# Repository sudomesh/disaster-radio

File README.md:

[disaster.radio](https://disaster.radio) is currently not actively developed and [seeks a new maintainer](https://github.com/sudomesh/disaster-radio/issues/110)

It is a work-in-progress long-range, low-bandwidth wireless disaster recovery mesh network powered by the sun. 

* [firmware/](./firmware) contains the main example code for ESP32 dev boards
* [src/](./src) contains the disaster radio library code used by the firmware and simulator
* [web/](./web) is the demo chat app served up by the disaster-radio
* [hardware/](./hardware) is the kicad board layout and schematic
* [enclosure/](./enclosure) are 3D models of the enclosure(s)
* [android app](https://github.com/beegee-tokyo/disaster-radio-android) source code for [DisasterRadio BLE Chatbox](https://play.google.com/store/apps/details?id=tk.giesecke.disaster_radio&hl=en_US) Android Application
* [mapping web app](https://github.com/sudomesh/disaster-radio-map) source code for mapping web-based appilcation

## Table of contents
- [Getting Started](#getting-started)
- [Layout and Flow](#layout-and-flow)
- [Hardware Connections](#hardware-connections)
- [Initial Setup with PlatformIO](#initial-setup-with-platformio)
    - [Building firmware](#building-firmware)
    - [Flashing firmware](#flashing-firmware)
        - [For dev boards](#for-dev-boards)
- [Building Web App](#building-web-app)
    - [Building and uploading SPIFFS image](#building-and-uploading-SPIFFS-image)
- [Testing Firmware](#testing-firmware) 
- [Adding Libraries](#adding-libraries)
- [Creating Binary for Release](#creating-binary-for-release)
- [License](#license)

# Getting Started
The quickest way to get started with disaster.radio is to buy a <a href="https://www.aliexpress.com/item/4000396836096.html" target="_blank">preinstalled device</a> or
* Download the [latest release](https://github.com/sudomesh/disaster-radio/releases)
* Unzip the `disaster-radio-0.X.X.zip` file
* Follow the included instructions for flashing it to your device

If you would rather test the latest, cutting-edge developments, you can compile the firmware yourself by cloning this repo and following the [initial setup](#initial-setup-with-platformio) instructions.

# Layout and Flow
The Disaster Radio firmware is made up of a single "server" and a number of "clients", as well as "middleware" that sits between the clients and server. These are a"server" and "clients" in the logical, software sense, not a literal, networking sense.
 
Here are the modules currently implemented with descriptions of their purpose:
- DisasterServer:  
    - DisasterRadio: the main "server" that takes messages from clients and sends them to other clients

- DisasterClient:  
    - LoRaClient: interfaces with LoRaLayer2  
    - WebSocketClient: WebSocket connections from the web app  
    - StreamClient: for Arduino Stream, currently used for serial console  
    - TCPClient: for a telnet-like server  
    - HistoryRecord: records messages to SD card (or bounded queue in memory)  
    - OLEDClient: displays messages on the screen (mostly for debugging purposes, but eventually I'd like to use this for a mobile Disaster Radio terminal of some kind)   
    - GPSClient: proof-of-concept, interfaces with a serial GPS module to beacon your current location periodically  

- DisasterMiddleware:  
    - WelcomeMessage: (very simple, in main.cpp) shows a welcome message to clients when they connect
    - HistoryReplay: shows history to clients when they connect
    - Console: implements a simple console with chat (similar to the web app) plus some /commands (I went with a more IRC-like syntax but you could easily implement a getopt version)
    
- DisasterHistory:
    - HistorySD: records history to SD card
    - HistoryMemory: records history to a bounded queue in memory (default limit 10 messages)

The server and clients communicate with each other using "datagrams" that include a destination address, a message type, and a message. Read more about the disaster radio networking stack on our wiki, https://github.com/sudomesh/disaster-radio/wiki/Layered-Model.

# Hardware Connections  

For supported development boards see the [Devices & Hardware](https://github.com/sudomesh/disaster-radio/wiki/Devices--&-Hardware) wiki page.  

The pinouts for supported boards can be found in [firmware/esp32/config.h](https://github.com/sudomesh/disaster-radio/blob/master/firmware/esp32/config.h).  

DIO0 sends an interrupt from the LoRa transceiver upon Tx/Rx Ready on the radio.   
Chip selects can be used to explicitly switch between the LoRa tranceiver and the SD card; however, the SD card should be enabled by default, as the LoRa interrupt appears to handle enabling the transceiver (note: this still needs to be thoroughly tested, what happens if you receive an interrupt while loading from the SD?).  

# Initial Setup with PlatformIO

```
pip install -U platformio
```

Edit `platformio.ini` to suit your needs. If you are flashing a ESP32 LILY TTGO board then you will probably not have to edit anything in `platformio.ini` but make sure `upload_port` is set to the correct device which may vary depending on your operating system and which other devices you have connected.

## Building firmware

To test that the firmware is compiling correctly without flashing it to a device, run
```
pio run
```

This will compile all libraries and main firmware files. The resulting binary is stored as `.pio/build/ttgo-lora32-v1/firmware.bin`

## Flashing firmware

### For dev boards

Connect your computer to the board using a usb cable,

In `platformio.ini` make sure `upload_port`, `upload_speed`, etc are correct for your device.

Then run:

```
pio run -t upload
```
 
By default, PlatformIO builds and flashes firmware for the LILY's ESP32 TTGO V2 dev board. If you would like to build for another supported board, select the corresponding build environment. For example to build and flash the firmware and file system for the ESP32 TTG0 V1 board, use the following, 

```
pio run -e ttgo-lora32-v1 -t upload -t uploadfs

```

## Developing firmware

Some useful hints for developing this firmware using platformio are included here,
* It may be a good idea to delete the libdeps folder prior to rebuilding, as old, out-dated libraries could case conflits. To do this, `rm -rf .pio/libdeps`.
* If you would like to make changes to a specific library, such as LoRaLayer2, you can clone the library into the `firmware/lib` folder that is created after running `pio run` and then comment it out or remove it from the `lib_deps` list in the `platformio.ini` file.

# Building Web App

First, build the web app using npm, instructions for can be found in [web/README.md](https://github.com/sudomesh/disaster-radio/tree/master/web#setup).

If you have trouble building the web app with npm, you can download a pre-built version of web app as part of the [latest release](https://github.com/sudomesh/disaster-radio/releases). Then, copy the files in `web/static/` from the zipped release to the `web/static/` directory in the cloned repo.

## Building and uploading SPIFFS image

Next, build the binary for the SPIFFS and upload it to your board.

To only build:

```
pio run -t buildfs
```

To build and upload:

```
pio run -t uploadfs
```

If using an SD card, copy the contents of `web/static/` to the root of a fat32 formatted SD card, then insert the SD card.

# Testing Firmware  
Once the firmware and SPIFFS image has been successfully flashed, you can test it by logging into the `disaster.radio <node-address>` wireless network and navigating to http://192.168.4.1 in a browser to access the demo chat app.  

You can also try connecting to the device via serial or telnet with commands like,  
```
pio device monitor
```
or
```
telnet 192.168.4.1
```

After pressing enter once, you should be greeted with a banner and presented with a prompt to enter a nick or send an anonymous message,
```
     ___              __                            ___    
 ___/ (_)__ ___ ____ / /____ ____      _______ ____/ (_)__ 
/ _  / (_-</ _ `(_-</ __/ -_) __/ _   / __/ _ `/ _  / / _ \
\_,_/_/___/\_,_/___/\__/\__/_/   (_) /_/  \_,_/\_,_/_/\___/
v1.0.0-rc.2
LoRa transceiver connected
Local address of your node is 1d69bd4c
Type '/join NICKNAME' to join the chat, or '/help' for more commands.
< > 
```

See [firmware/README.md](https://github.com/sudomesh/disaster-radio/tree/master/firmware) for more debugging information.

# Adding Libraries

If you're including new libraries in the firmware, for PlatformIO, you wil need to add them to `platformio.ini` under `lib_deps`.

# Creating Binary for Release

A full binary image can be created by reading the flash contents of a ESP32 that is flashed with the latest release of the firmware.
To do this, run the following command,
```
esptool.py -p /dev/ttyUSB0 -b 921600 read_flash 0 0x400000 esp_flash.bin
```

This can then be flashed to a new device like so,
```
esptool.py -p /dev/ttyUSB0 --baud 460800 write_flash 0x00000 esp_flash.bin
```

# License

* `firmware/`: Dual licensed under both GPLv3 and AGPLv3
* `web/`: AGPLv3

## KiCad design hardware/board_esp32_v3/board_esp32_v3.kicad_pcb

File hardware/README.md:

# Hardware

The disaster.radio hardware is as open-as-possible. Currently, we have the schematic, BOM, and circuit board design for a development board that you can, theoretically, print yourself or order from a circuit board manufacturer of your choice. 

## Features
* ESP32-WROOM integrated WiFi + BLE microcontroller
* Dual LoRa modules
* Micro-SD card slot
* Micro-USB port for serial debugging
* Battery connection
* Battery charging module (currently using TPS6216)

## Developement
Our hardware was designed in KiCad, if you would like to edit the board deisgn or take a closer look at the schematics you can [download and install KiCad](https://kicad-pcb.org/download/) for your system.

After installing, open KiCad, choose `File > Open Project...`, navigate to where you cloned this repo, and select the file `hardware/board_esp32_v2/board_esp32_v2.pro`. You can now open and view the schematic and pcb design.

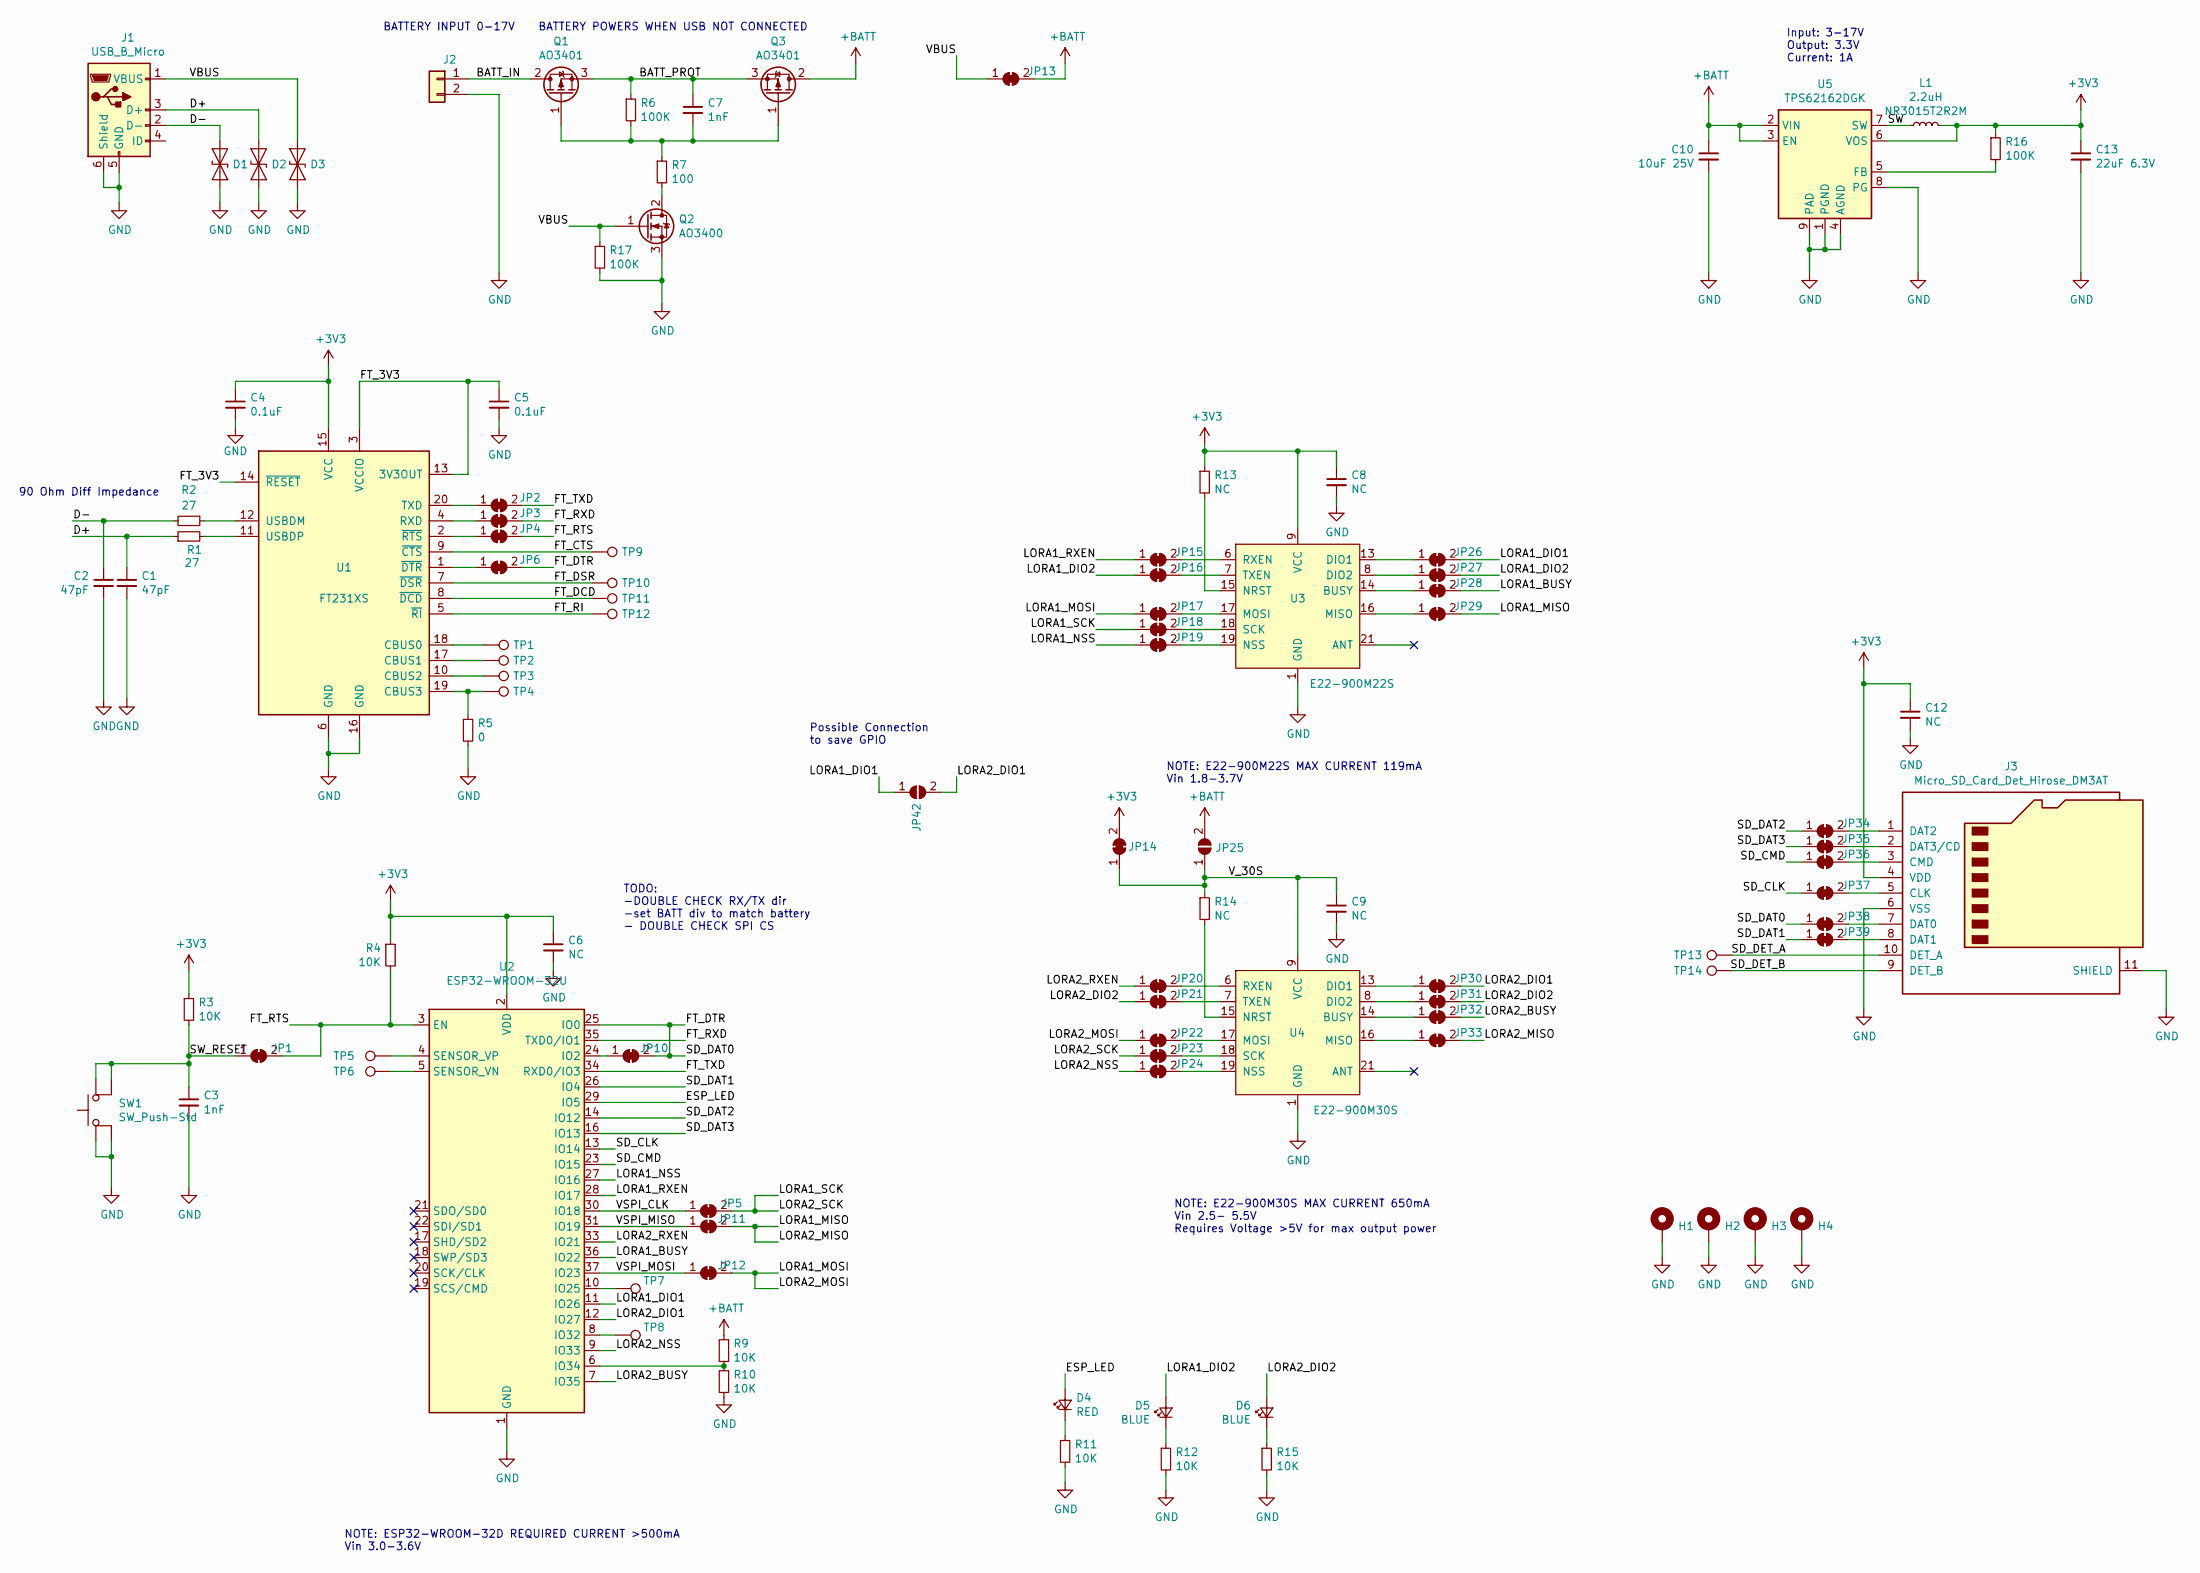
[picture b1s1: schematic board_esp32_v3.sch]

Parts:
C1, C2: 47pF; C_0402_1005Metric
C3, C7: 1nF; C_0402_1005Metric
C4, C5: 0.1uF; C_0402_1005Metric
C6, C8, C9, C12: NC; C_0402_1005Metric
C10: 10uF 25V; C_0805_2012Metric
C13: 22uF 6.3V; C_0805_2012Metric
D1, D2, D3: TPD1E10B06; D_0402_1005Metric
D4: RED; LED_0603_1608Metric
D5, D6: BLUE; LED_0603_1608Metric
H1, H2, H3, H4: MountingHole_Pad; MountingHole_2.2mm_M2_ISO7380_Pad
J1: USB_B_Micro; USB_Micro-B_GCT_USB3076-30-A_handsolder
J2: Conn_01x02; PinHeader_1x02_P2.54mm_Vertical
J3: Micro_SD_Card_Det_Hirose_DM3AT; microSD_HC_Hirose_DM3D-SF
JP1, JP2, JP3, JP4, JP5, JP6, JP10, JP11, JP12, JP13, JP14, JP15, JP16, JP17, JP18, JP19, JP20, JP21, JP22, JP23, JP24, JP26, JP27, JP28, JP29, JP30, JP31, JP32, JP33, JP34, JP35, JP36, JP37, JP38, JP39: SolderJumper_2_Bridged; SolderJumper-2_P1.3mm_Bridged_RoundedPad1.0x1.5mm
JP25, JP42: SolderJumper_2_Open; SolderJumper-2_P1.3mm_Open_RoundedPad1.0x1.5mm
L1: 2.2uH; L_Taiyo-Yuden_NR-30xx_HandSoldering; MPN NR3015T2R2M
Q1, Q3: AO3401; SOT-23
Q2: AO3400; SOT-23
R1, R2: 27; R_0402_1005Metric
R3, R4, R9, R10, R11, R12, R15: 10K; R_0402_1005Metric
R5: 0; R_0402_1005Metric
R6, R16, R17: 100K; R_0402_1005Metric
R7: 100; R_0402_1005Metric
R13, R14: NC; R_0402_1005Metric
SW1: SW_Push-Std; SW_PUSH_6mm
TP1, TP2, TP3, TP4, TP9, TP10, TP11, TP12, TP13, TP14: TestPoint; TestPoint_Pad_D1.0mm
TP5, TP6, TP7, TP8: TP_HOLE; TestPoint_Pad_D1.0mm
U1: FT231XS; SSOP-20_3.9x8.7mm_P0.635mm
U2: ESP32-WROOM-32U
U3: E22-900M22S; E22_900T22S
U4: E22-900M30S
U5: TPS62162DGK; TPS62162DSGT

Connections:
+3V3: C4.1, C6.1, C8.1, C12.1, C13.1, J3.4 (VDD), JP14.2 (B), L1.2, R3.1, R4.1, R13.1, R16.1, U1.15 (VCC), U2.2 (VDD), U3.9 (VCC), U5.6 (VOS)
+BATT: C10.1, JP13.2 (B), JP25.2 (B), Q3.2 (D), R9.1, U5.2 (VIN), U5.3 (EN)
/BATT_IN: J2.1, Q1.2 (D)
/BATT_PROT: C7.1, Q1.3 (S), Q3.3 (S), R6.1
/D+: C1.1, D2.1 (A1), J1.3 (D+), R1.1
/D-: C2.1, D1.1 (A1), J1.2 (D-), R2.2
/ESP_LED: D4.2 (A), U2.29 (IO5)
/FT_3V3: C5.1, U1.3 (VCCIO), U1.13 (3V3OUT), U1.14 (~RESET)
/FT_CTS: TP9.1, U1.9 (~CTS)
/FT_DCD: TP11.1, U1.8 (~DCD)
/FT_DSR: TP10.1, U1.7 (~DSR)
/FT_DTR: JP6.2 (B), JP10.2 (B), JP38.1 (A), U2.25 (IO0)
/FT_RI: TP12.1, U1.5 (~RI)
/FT_RTS: JP1.2 (B), JP4.2 (B), R4.2, U2.3 (EN)
/FT_RXD: JP3.2 (B), U2.35 (TXD0/IO1)
/FT_TXD: JP2.2 (B), U2.34 (RXD0/IO3)
/LORA1_BUSY: JP28.2 (B), U2.36 (IO22)
/LORA1_DIO1: JP26.2 (B), JP42.1 (A), U2.11 (IO26)
/LORA1_DIO2: D5.2 (A), JP16.1 (A), JP27.2 (B)
/LORA1_MISO: JP11.2 (B), JP29.2 (B), JP33.2 (B)
/LORA1_MOSI: JP12.2 (B), JP17.1 (A), JP22.1 (A)
/LORA1_NSS: JP19.1 (A), U2.27 (IO16)
/LORA1_RXEN: JP15.1 (A), U2.28 (IO17)
/LORA1_SCK: JP5.2 (B), JP18.1 (A), JP23.1 (A)
/LORA2_BUSY: JP32.2 (B), U2.7 (IO35)
/LORA2_DIO1: JP30.2 (B), JP42.2 (B), U2.12 (IO27)
/LORA2_DIO2: D6.2 (A), JP21.1 (A), JP31.2 (B)
/LORA2_NSS: JP24.1 (A), U2.9 (IO33)
/LORA2_RXEN: JP20.1 (A), U2.33 (IO21)
/SD_CLK: JP37.1 (A), U2.13 (IO14)
/SD_CMD: JP36.1 (A), U2.23 (IO15)
/SD_DAT1: JP39.1 (A), U2.26 (IO4)
/SD_DAT2: JP34.1 (A), U2.14 (IO12)
/SD_DAT3: JP35.1 (A), U2.16 (IO13)
/SD_DET_A: J3.10 (DET_A), TP13.1
/SD_DET_B: J3.9 (DET_B), TP14.1
/SW: L1.1, U5.7 (SW)
/SW_RESET: C3.1, JP1.1 (A), R3.2, SW1.2
/VBUS: D3.1 (A1), J1.1 (VBUS), JP13.1 (A), Q2.1 (G), R17.1
/VSPI_CLK: JP5.1 (A), U2.30 (IO18)
/VSPI_MISO: JP11.1 (A), U2.31 (IO19)
/VSPI_MOSI: JP12.1 (A), U2.37 (IO23)
/V_30S: C9.1, JP14.1 (A), JP25.1 (A), R14.1, U4.9 (VCC), U4.10 (VCC)
GND: C1.2, C2.2, C3.2, C4.2, C5.2, C6.2, C8.2, C9.2, C10.2, C12.2, C13.2, D1.2 (A2), D2.2 (A2), D3.2 (A2), H1.1, H2.1, H3.1, H4.1, J1.5 (GND), J1.6 (Shield), J2.2, J3.6 (VSS), J3.11 (SHIELD), Q2.3 (S), R5.2, R10.2, R11.2, R12.2, R15.2, R17.2, SW1.1, U1.6 (GND), U1.16 (GND), U2.1 (GND), U2.15 (GND), U2.38 (GND), U2.39 (GND), U3.1 (GND), U3.2 (GND), U3.3 (GND), U3.4 (GND), U3.5 (GND), U3.10 (GND), U3.11 (GND), U3.12 (GND), U3.20 (GND), U3.22 (GND), U4.1 (GND), U4.2 (GND), U4.3 (GND), U4.4 (GND), U4.5 (GND), U4.11 (GND), U4.12 (GND), U4.20 (GND), U4.22 (GND), U5.1 (PGND), U5.4 (AGND), U5.8 (PG), U5.9 (PAD)
unnamed: C7.2, Q1.1 (G), Q3.1 (G), R6.2, R7.1
unnamed: D4.1 (K), R11.1
unnamed: D5.1 (K), R12.1
unnamed: D6.1 (K), R15.1
unnamed: J3.1 (DAT2), JP34.2 (B)
unnamed: J3.2 (DAT3/CD), JP35.2 (B)
unnamed: J3.3 (CMD), JP36.2 (B)
unnamed: J3.5 (CLK), JP37.2 (B)
unnamed: J3.7 (DAT0), JP38.2 (B)
unnamed: J3.8 (DAT1), JP39.2 (B)
unnamed: JP2.1 (A), U1.20 (TXD)
unnamed: JP3.1 (A), U1.4 (RXD)
unnamed: JP4.1 (A), U1.2 (~RTS)
unnamed: JP6.1 (A), U1.1 (~DTR)
unnamed: JP10.1 (A), U2.24 (IO2)
unnamed: JP15.2 (B), U3.6 (RXEN)
unnamed: JP16.2 (B), U3.7 (TXEN)
unnamed: JP17.2 (B), U3.17 (MOSI)
unnamed: JP18.2 (B), U3.18 (SCK)
unnamed: JP19.2 (B), U3.19 (NSS)
unnamed: JP20.2 (B), U4.6 (RXEN)
unnamed: JP21.2 (B), U4.7 (TXEN)
unnamed: JP22.2 (B), U4.17 (MOSI)
unnamed: JP23.2 (B), U4.18 (SCK)
unnamed: JP24.2 (B), U4.19 (NSS)
unnamed: JP26.1 (A), U3.13 (DIO1)
unnamed: JP27.1 (A), U3.8 (DIO2)
unnamed: JP28.1 (A), U3.14 (BUSY)
unnamed: JP29.1 (A), U3.16 (MISO)
unnamed: JP30.1 (A), U4.13 (DIO1)
unnamed: JP31.1 (A), U4.8 (DIO2)
unnamed: JP32.1 (A), U4.14 (BUSY)
unnamed: JP33.1 (A), U4.16 (MISO)
unnamed: Q2.2 (D), R7.2
unnamed: R1.2, U1.11 (USBDP)
unnamed: R2.1, U1.12 (USBDM)
unnamed: R5.1, TP4.1, U1.19 (CBUS3)
unnamed: R9.2, R10.1, U2.6 (IO34)
unnamed: R13.2, U3.15 (NRST)
unnamed: R14.2, U4.15 (NRST)
unnamed: R16.2, U5.5 (FB)
unnamed: TP1.1, U1.18 (CBUS0)
unnamed: TP2.1, U1.17 (CBUS1)
unnamed: TP3.1, U1.10 (CBUS2)
unnamed: TP5.1, U2.4 (SENSOR_VP)
unnamed: TP6.1, U2.5 (SENSOR_VN)
unnamed: TP7.1, U2.10 (IO25)
unnamed: TP8.1, U2.8 (IO32)

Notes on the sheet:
90 Ohm Diff Impedance
NOTE: ESP32-WROOM-32D REQUIRED CURRENT >500mA Vin 3.0-3.6V
BATTERY INPUT 0-17V
BATTERY POWERS WHEN USB NOT CONNECTED
TODO: -DOUBLE CHECK RX/TX dir -set BATT div to match battery - DOUBLE CHECK SPI CS
Possible Connection to save GPIO
NOTE: E22-900M22S MAX CURRENT 119mA Vin 1.8-3.7V
NOTE: E22-900M30S MAX CURRENT 650mA Vin 2.5- 5.5V Requires Voltage >5V for max output power
Input: 3-17V Output: 3.3V Current: 1A

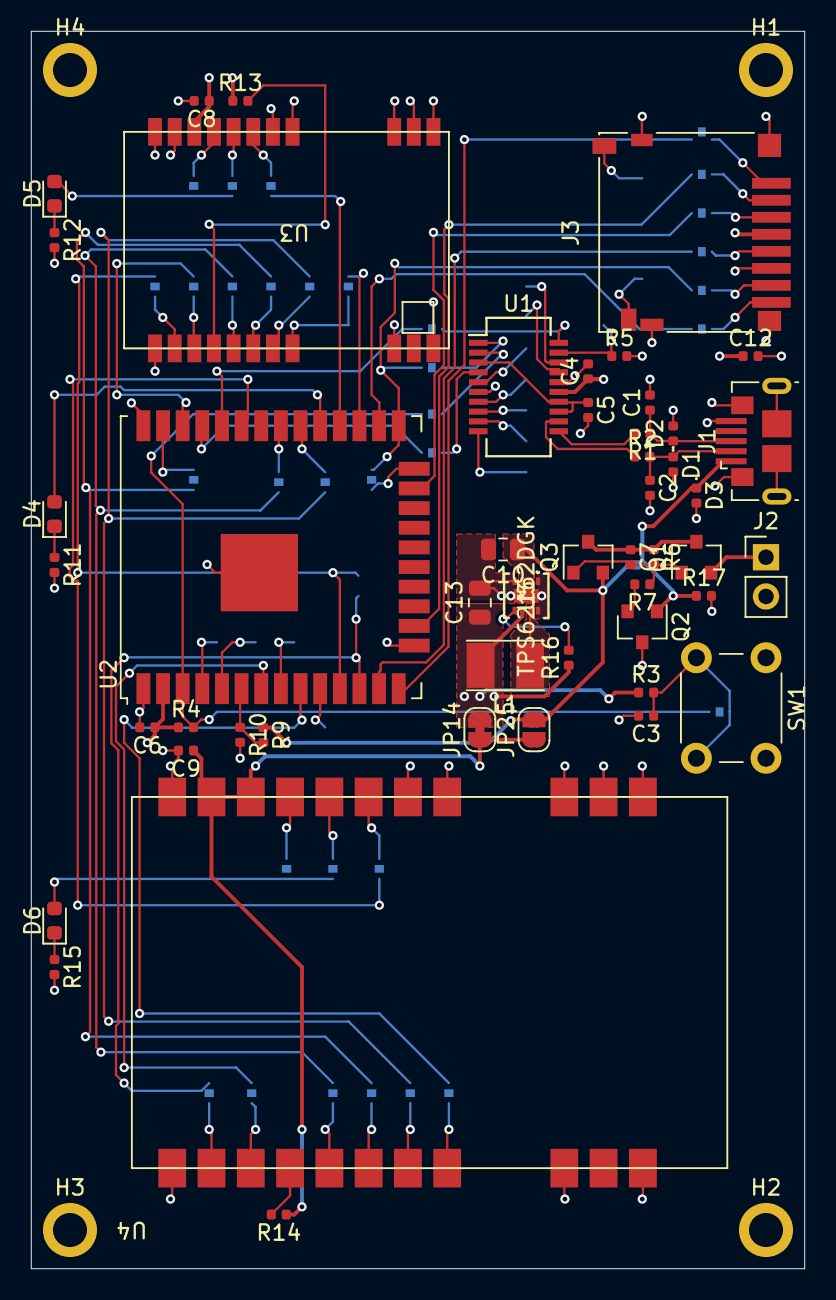
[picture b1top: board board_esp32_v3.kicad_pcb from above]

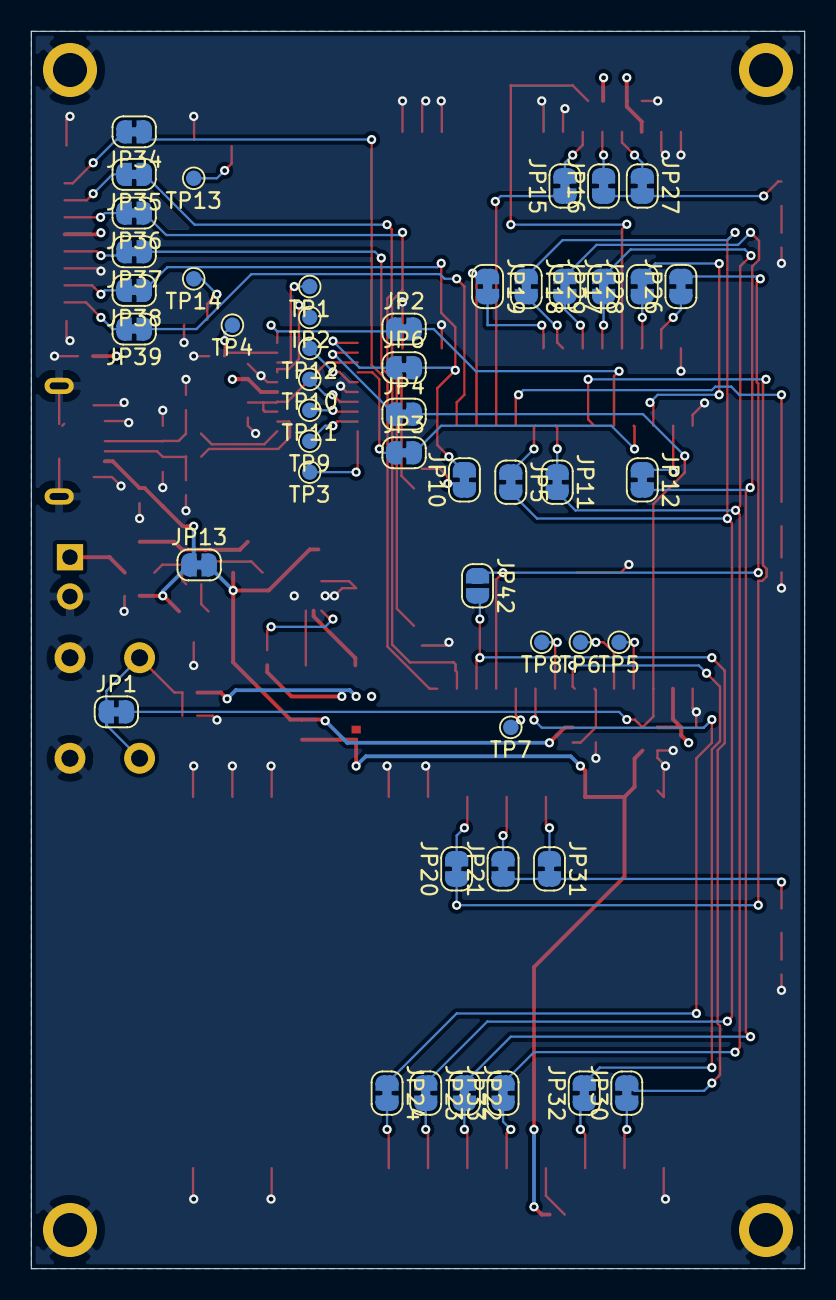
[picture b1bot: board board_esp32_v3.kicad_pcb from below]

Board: 4 copper layers, 50.0 x 80.0 mm, 102 parts (49 on the bottom side), 92 nets.

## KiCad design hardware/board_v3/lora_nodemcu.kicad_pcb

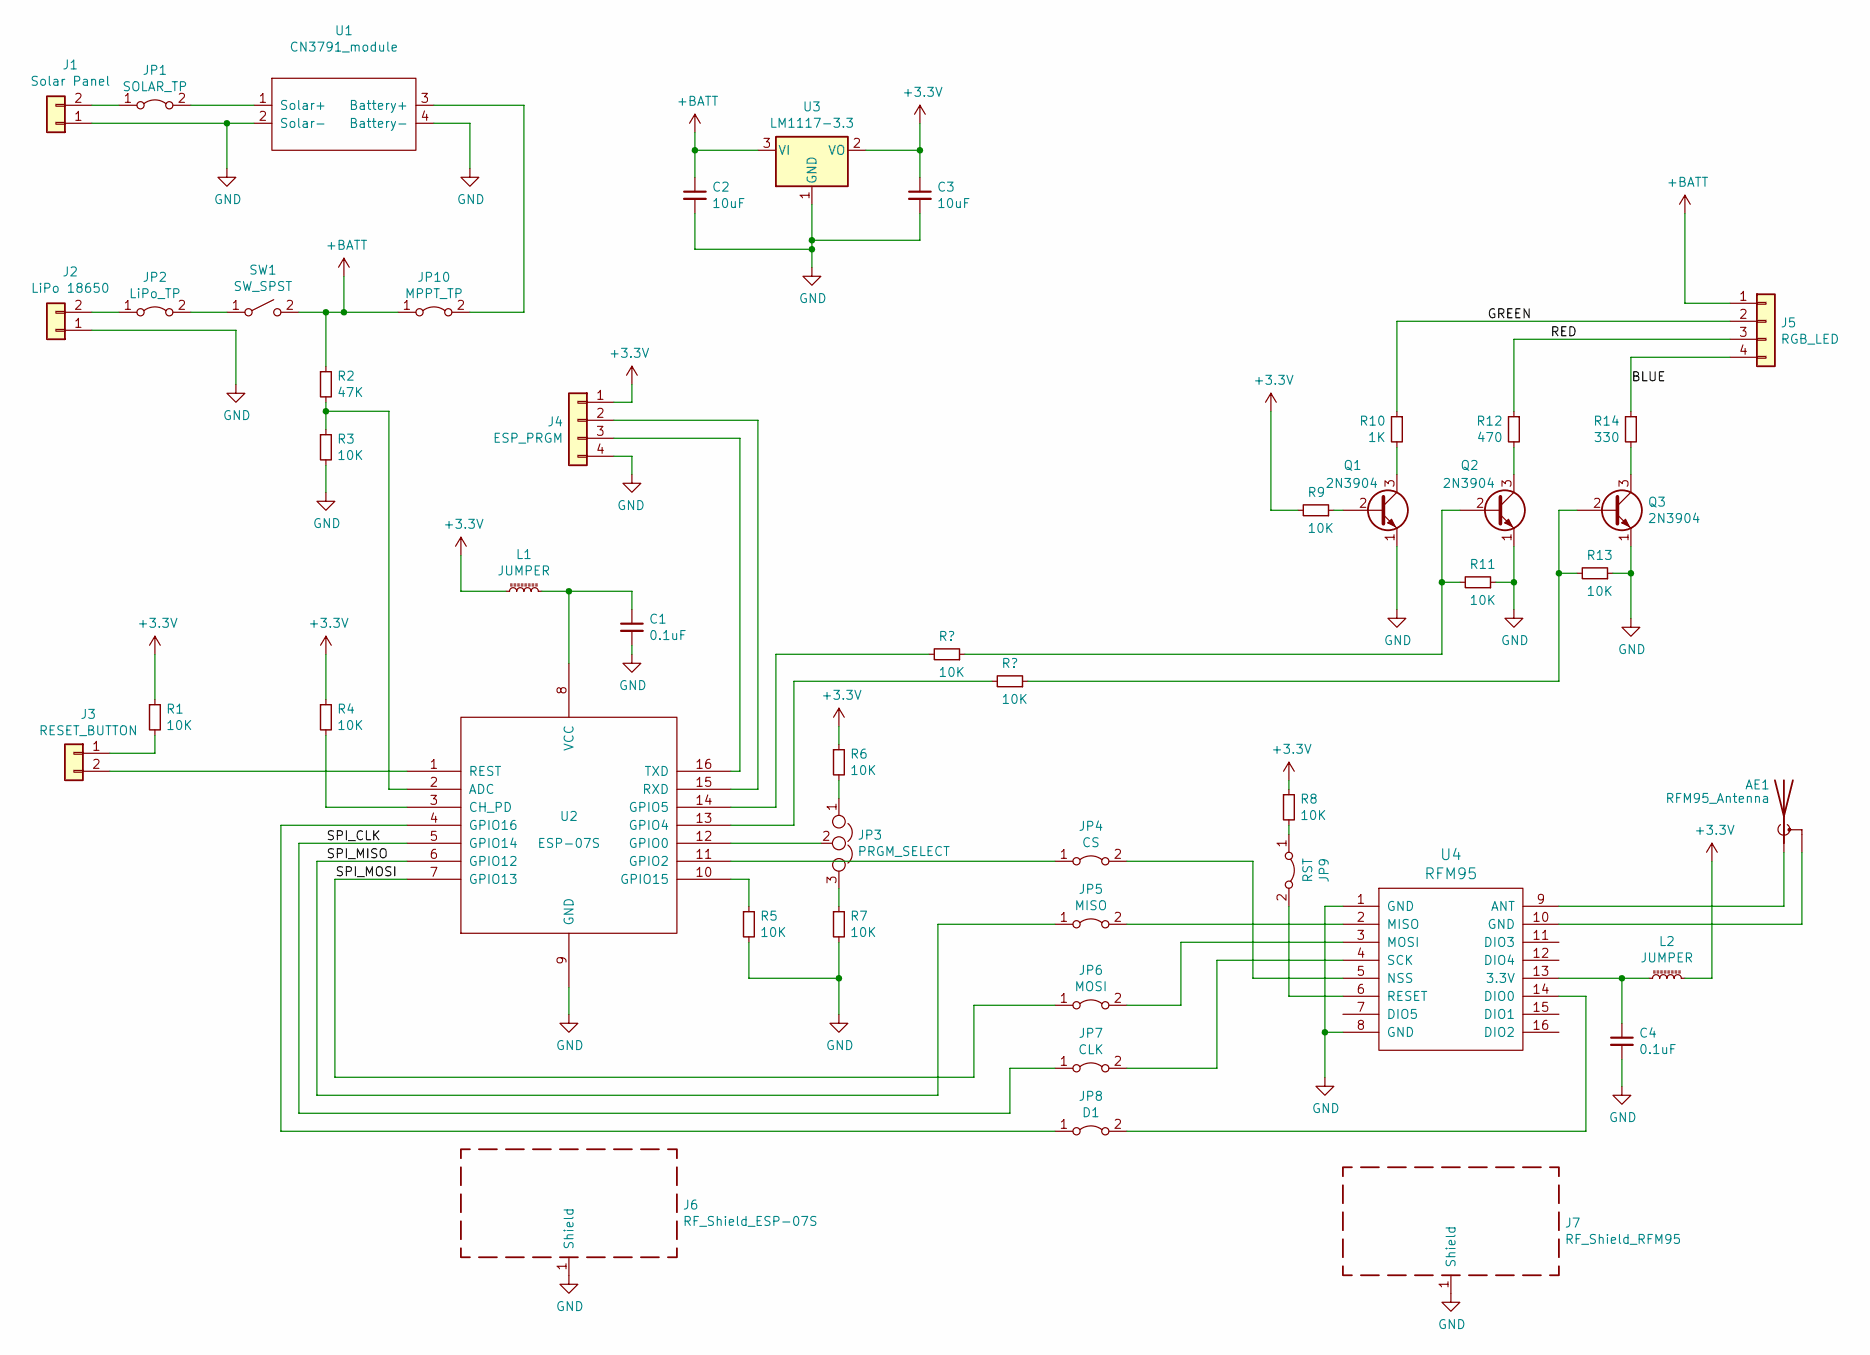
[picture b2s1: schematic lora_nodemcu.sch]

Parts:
AE1: RFM95_Antenna; U.FL_Hirose_U.FL-R-SMT-1_Vertical
C1, C4: 0.1uF; C_0805_2012Metric_Pad1.15x1.50mm_HandSolder
C2, C3: 10uF; C_0805_2012Metric_Pad1.15x1.50mm_HandSolder
J1: Solar Panel; PhoenixContact_MCV_1,5_2-G-5.08_1x02_P5.08mm_Vertical
J2: LiPo 18650; BatteryHolder_MPD_BH-18650-PC2
J3: RESET_BUTTON; PhoenixContact_MCV_1,5_2-G-5.08_1x02_P5.08mm_Vertical
J4: ESP_PRGM; PinHeader_1x04_P2.54mm_Vertical
J5: RGB_LED; PhoenixContact_MCV_1,5_4-G-5.08_1x04_P5.08mm_Vertical
J6: RF_Shield_ESP-07S; Wuerth_36103305_30x30mm
J7: RF_Shield_RFM95; Wuerth_36103305_30x30mm
JP1: SOLAR_TP; SolderJumper-2_P1.3mm_Bridged_Pad1.0x1.5mm
JP2: LiPo_TP; SolderJumper-2_P1.3mm_Bridged_Pad1.0x1.5mm
JP3: PRGM_SELECT; PinHeader_1x03_P2.54mm_Vertical
JP4: CS; SolderJumper-2_P1.3mm_Bridged_Pad1.0x1.5mm
JP5: MISO; SolderJumper-2_P1.3mm_Bridged_Pad1.0x1.5mm
JP6: MOSI; SolderJumper-2_P1.3mm_Bridged_Pad1.0x1.5mm
JP7: CLK; SolderJumper-2_P1.3mm_Bridged_Pad1.0x1.5mm
JP8: D1; SolderJumper-2_P1.3mm_Bridged_Pad1.0x1.5mm
JP9: RST; SolderJumper-2_P1.3mm_Bridged_Pad1.0x1.5mm
JP10: MPPT_TP; SolderJumper-2_P1.3mm_Bridged_Pad1.0x1.5mm
L1, L2: JUMPER; L_0805_2012Metric_Pad1.15x1.50mm_HandSolder
Q1, Q2, Q3: 2N3904; SOT-23_Handsoldering
R1, R3, R4, R5, R6, R7, R8, R9, R11, R13: 10K; R_0805_2012Metric_Pad1.15x1.50mm_HandSolder
R2: 47K; R_0805_2012Metric_Pad1.15x1.50mm_HandSolder
R10: 1K; R_0805_2012Metric_Pad1.15x1.50mm_HandSolder
R12: 470; R_0805_2012Metric_Pad1.15x1.50mm_HandSolder
R14: 330; R_0805_2012Metric_Pad1.15x1.50mm_HandSolder
SW1: SW_SPST; PhoenixContact_MCV_1,5_2-G-5.08_1x02_P5.08mm_Vertical
U1: CN3791_module
U2: ESP-07S
U3: LM1117-3.3; SOT-223-3_TabPin2
U4: RFM95

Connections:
+3V3: C3.1, J4.1, L1.1, L2.2, R1.1, R4.1, R6.1, R8.1, R9.2, U3.2 (VO)
+BATT: C2.1, J5.1, JP10.1 (A), R2.1, SW1.2 (B), U3.3 (VI); also elsewhere on the board
/3V3_ESP: C1.1, L1.2, U2.8 (VCC)
/3V3_RFM: C4.1, L2.1, U4.13 (3.3V)
/BATT_TP: JP10.2 (B), U1.3 (Battery+)
/BLUE: J5.4, R14.1; also elsewhere on the board
/GREEN: J5.2, R10.1; also elsewhere on the board
/LIPO_TP: JP2.2 (B), SW1.1 (A)
/RED: J5.3, R12.1; also elsewhere on the board
/SOLAR_CONN: J1.2, JP1.1 (A)
/SOLAR_TP: JP1.2 (B), U1.1 (Solar+)
/SPI_CLK: JP7.1 (A), U2.5 (GPIO14)
/SPI_MISO: JP5.1 (A), U2.6 (GPIO12)
/SPI_MOSI: JP6.1 (A), U2.7 (GPIO13)
unnamed: AE1.1 (A), U4.9 (ANT)
unnamed: AE1.2 (Shield), U4.10 (GND)
unnamed: J3.1, R1.2
unnamed: J3.2, U2.1 (REST)
unnamed: J4.2, U2.15 (RXD)
unnamed: J4.3, U2.16 (TXD)
unnamed: JP3.1, R6.2
unnamed: JP3.2, U2.12 (GPIO0)
unnamed: JP3.3, R7.1
unnamed: JP4.1 (A), U2.11 (GPIO2)
unnamed: JP4.2 (B), U4.5 (NSS)
unnamed: JP5.2 (B), U4.2 (MISO)
unnamed: JP6.2 (B), U4.3 (MOSI)
unnamed: JP7.2 (B), U4.4 (SCK)
unnamed: JP8.1 (A), U2.4 (GPIO16)
unnamed: JP8.2 (B), U4.14 (DIO0)
unnamed: JP9.1 (A), R8.2
unnamed: JP9.2 (B), U4.6 (RESET)
unnamed: Q1.2 (B), R9.1
unnamed: Q1.3 (C), R10.2
unnamed 34: Q2.2 (B), R11.2; also elsewhere on the board
unnamed: Q2.3 (C), R12.2
unnamed 36: Q3.2 (B), R13.2; also elsewhere on the board
unnamed: Q3.3 (C), R14.2
unnamed: R2.2, R3.1, U2.2 (ADC)
unnamed: R4.2, U2.3 (CH_PD)
unnamed: R5.1, U2.10 (GPIO15)
unnamed 41: U2.14 (GPIO5); also elsewhere on the board
unnamed 42: U2.13 (GPIO4); also elsewhere on the board

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
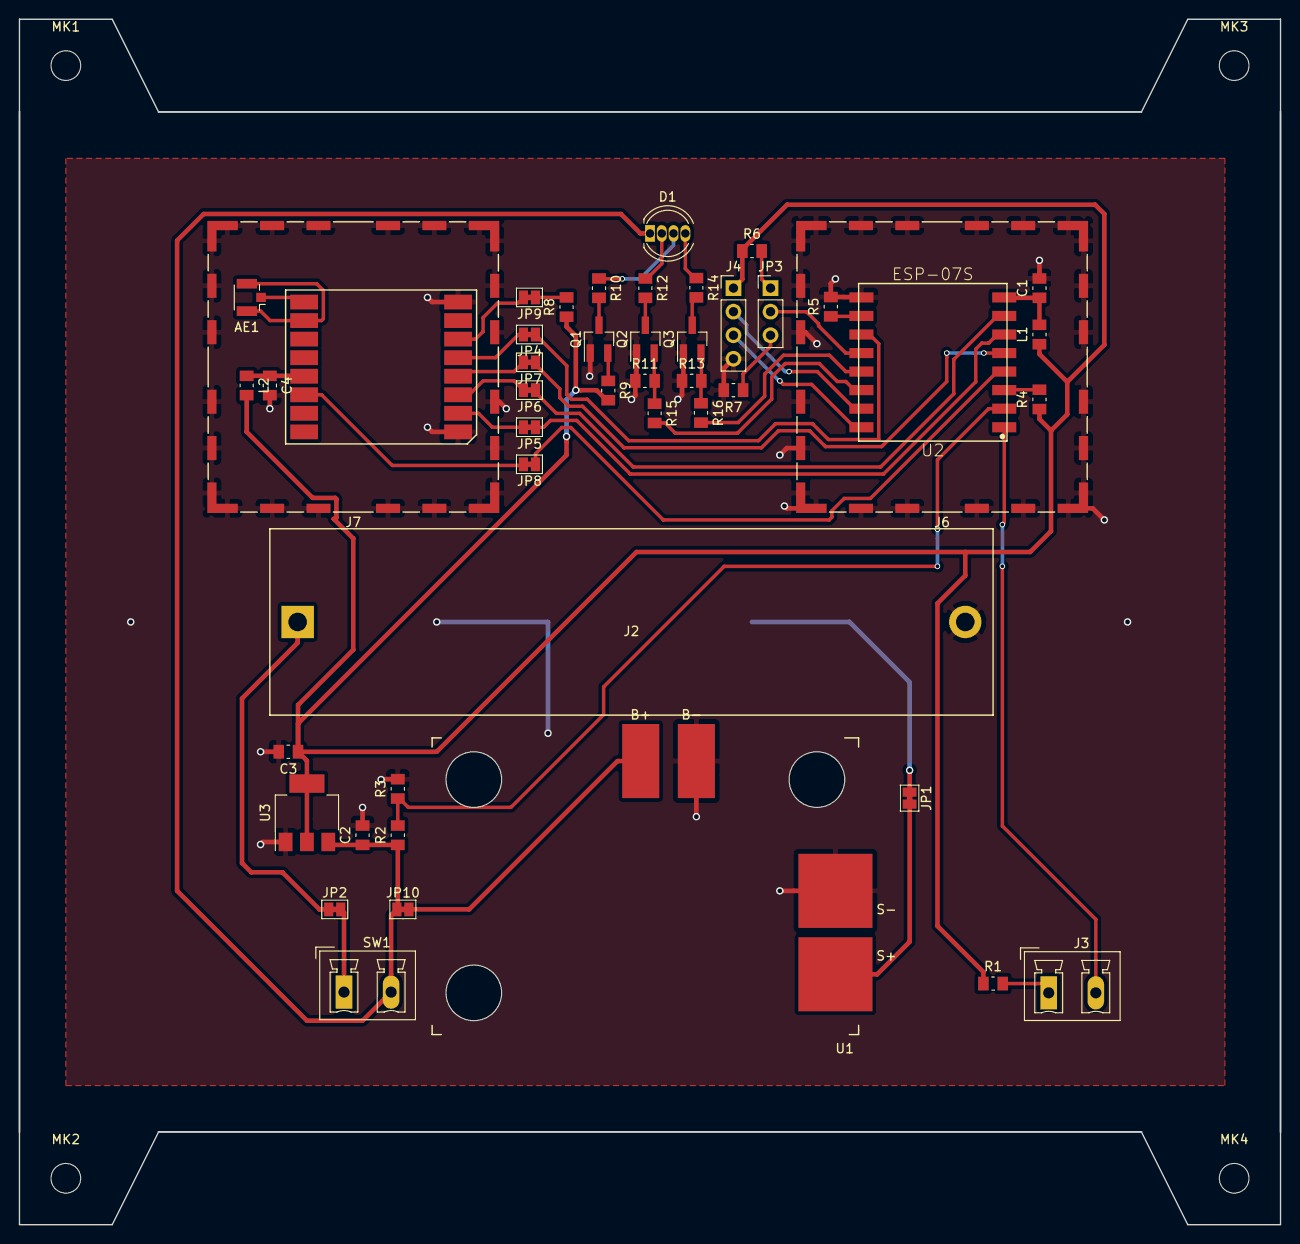
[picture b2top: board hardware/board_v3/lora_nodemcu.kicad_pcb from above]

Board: 2 copper layers, 136.0 x 130.0 mm, 52 parts (1 on the bottom side), 45 nets.

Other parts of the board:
D1: LED_ARGB; LED_D5.0mm-4
MK1, MK2, MK3, MK4: Mounting_Hole; MountingHole_3.2mm_M3
R15, R16: 10K; R_0805_2012Metric_Pad1.15x1.50mm_HandSolder

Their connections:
+BATT: D1.1; also elsewhere on the board
/BLUE: D1.4; also elsewhere on the board
/GREEN: D1.3; also elsewhere on the board
/RED: D1.2; also elsewhere on the board
unnamed 34: R15.1; also elsewhere on the board
unnamed 36: R16.1; also elsewhere on the board
unnamed 41: R15.2; also elsewhere on the board
unnamed 42: R16.2; also elsewhere on the board

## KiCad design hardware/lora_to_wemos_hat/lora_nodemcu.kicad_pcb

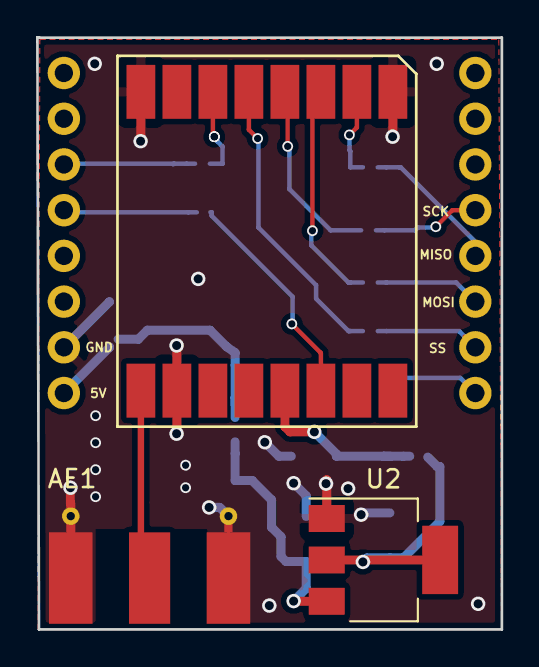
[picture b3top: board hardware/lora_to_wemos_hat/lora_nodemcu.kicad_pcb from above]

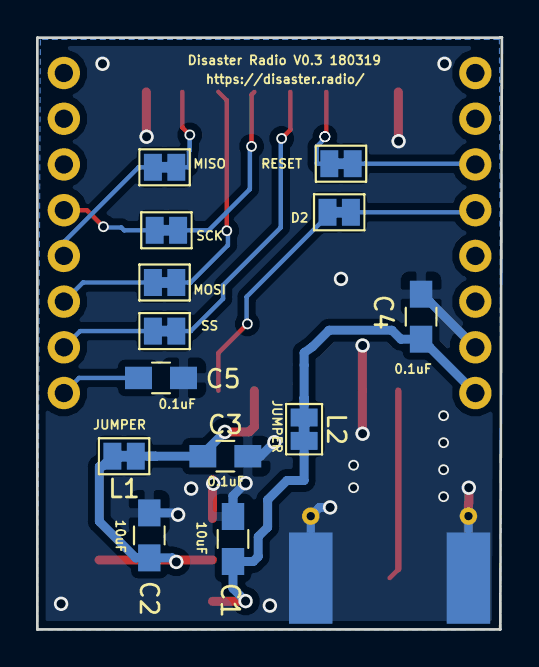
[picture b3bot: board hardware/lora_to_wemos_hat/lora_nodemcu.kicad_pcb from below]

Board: 4 copper layers, 25.8 x 32.9 mm, 17 parts (13 on the bottom side), 19 nets.

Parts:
AE1: Antenna_Shield; Molex_SMA_Jack_Edge_Mount
C1, C2: 10uF; C_0805_HandSoldering
C3, C4, C5: 0.1uF; C_0805_HandSoldering
L1, L2: JUMPER; SolderJumper-2_P1.3mm_Bridged_Pad1.0x1.5mm
R1, R2, R3, R4, R5, R6: JUMPER; SolderJumper-2_P1.3mm_Bridged_Pad1.0x1.5mm
U1: RFM95
U2: LM1117-3.3; SOT-223
U3: WeMos_mini; D1_mini_board

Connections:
+3V3: C2.2, L1.2, U2.2, U2.4
+5V: C1.2, L2.2, U2.3
/50Ohm: AE1.1, U1.9
/MISO: R5.1, U3.13
/MOSI: R6.1, U3.14
/RF95_3V3: C3.1, L1.1, U1.13
/SCK: R4.1, U3.12
/SS: R3.1, U3.15
/wemos_5V: C4.2, L2.1, U3.1
GND: AE1.2, C1.1, C2.1, C3.2, C4.1, C5.1, U1.1, U1.8, U1.10, U2.1, U3.2
unnamed: C5.2, U3.16
unnamed: R1.1, U3.5
unnamed: R1.2, U1.14
unnamed: R2.1, U3.6
unnamed: R2.2, U1.6
unnamed: R3.2, U1.5
unnamed: R4.2, U1.4
unnamed: R5.2, U1.2
unnamed: R6.2, U1.3

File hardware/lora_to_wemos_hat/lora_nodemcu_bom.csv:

"Id";"Designator";"Package";"Quantity";"Designation";"Supplier and ref";
1;"U3";"D1_mini_board";1;"WeMos_mini";;;
2;"C3,C5,C4";"C_0805_HandSoldering";3;"0.1uF";;;
3;"L2,L1";"L_0805_HandSoldering";2;"JUMPER";;;
4;"AE1";"Molex_SMA_Jack_Edge_Mount";1;"Antenna_Shield";;;
5;"C1,C2";"C_0805_HandSoldering";2;"10uF";;;
6;"R1,R2,R3,R4,R5,R6";"R_0805_HandSoldering";6;"JUMPER";;;
7;"U1";"RFM95";1;"RFM95";;;
8;"U2";"SOT-223";1;"LM1117-3.3";;;

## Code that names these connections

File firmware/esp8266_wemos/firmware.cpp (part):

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int beaconInterval = 30000;

// for portable node (wemos d1 mini) use these settings:
const int loraChipSelect = 15; // LoRa radio chip select, GPIO15 = D8 on WeMos D1 mini
const int resetPin = 5;       // LoRa radio reset, GPIO0 = D3 
const int irqPin = 4;        // interrupt pin for receive callback?, GPIO2 = D4

// for solar-powered module use these settings:
/*
const int csPin = 2;          // LoRa radio chip select, GPIO2
const int resetPin = 5;       // LoRa radio reset (hooked to LED, unused)
const int irqPin = 16;        // interrupt pin for receive callback?, GPIO16
*/

const int SDChipSelect = 2;
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

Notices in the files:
parts and their libraries:
Copyright 2016 Accelerated Designs. All rights reserved.
